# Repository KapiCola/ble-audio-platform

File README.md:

# BLE Audio Platform - Engineering Project

Custom hardware and firmware platform for prototyping and evaluating Bluetooth Low Energy Audio broadcast transmission.

This repository combines:
- custom PCB design created in KiCad
- firmware applications based on nRF Connect SDK and Zephyr RTOS
- component datasheets used during design and bring-up
- test logs and recorded audio collected during BLE Audio experiments

The platform is built around the BT40F SiP with the Nordic nRF5340 and was used to evaluate LE Audio broadcast transmission based on BIS streams.

## System Overview

Main hardware blocks:
- BT40F SiP with Nordic nRF5340
- Nordic nPM13xx PMIC (nPM1304 used in the assembled board as a practical substitute for nPM1300; the main functional difference is reduced battery-charging capability)
- CP2105 USB-UART bridge
- SGTL5000 external audio codec
- USB-C power and debug connectivity
- microphone, line output, and headphone audio connectors

## Repository Layout

```text
.
|-- Datasheets/   Component datasheets used during design and bring-up
|-- Firmware/     Zephyr/NCS applications, overlays, and helper modules
|-- Images/       Board photos, PCB renders, and architecture diagrams
|-- KiCad/        Schematic, PCB, project libraries, and Gerber outputs
`-- Tests_data/   Recorded audio samples and test logs
```

Important subdirectories:
- `Firmware/bap_broadcast_source/` BLE Audio broadcast source application
- `Firmware/bap_broadcast_sink/` BLE Audio broadcast sink application
- `Firmware/codec_test/` codec bring-up and audio-path verification
- `Firmware/test_i2c/` I2C and peripheral detection tests
- `Firmware/leds_test/` PMIC and LED bring-up
- `Firmware/beacon/` BLE beacon baseline application
- `Firmware/biblioteki/` shared helper modules such as `pmic` and `i2c_helpers`
- `KiCad/BT40F_audio_board_smaller/` main KiCad project
- `KiCad/Gerber/` exported manufacturing files
- `Tests_data/Test_Logs/` logs from lab and real-world experiments
- `Tests_data/Recorded_Audio/` captured audio files used during evaluation

Note: some directories inside `Firmware/` such as `build/`, `Build_V1/`, and `MyBoard/` are generated build outputs committed alongside the source tree. They are useful as build records, but they are not the primary source files to edit.

## Firmware Summary

The main project flow is built around two applications:
- `bap_broadcast_source` transmits BLE Audio broadcast streams
- `bap_broadcast_sink` receives BLE Audio broadcasts and contains project-specific modules for LC3 handling, USB, codec output, and stream reception

Additional applications are included for hardware validation and bring-up:
- `codec_test` initializes and probes the SGTL5000 path
- `test_i2c` verifies low-level I2C communication and peripheral presence
- `leds_test` validates PMIC-related control paths and LED behavior
- `beacon` provides a minimal BLE reference application

The per-application `README.rst` files under `Firmware/` are based on upstream Zephyr samples. For this repository, the project-specific behavior is defined mainly by the local `src/`, `boards/`, `*.overlay`, `prj.conf`, and `Kconfig*` files.

## Hardware Design

The hardware project contains:
- schematic and PCB layout files in `KiCad/BT40F_audio_board_smaller/`
- custom symbol and footprint libraries in `KiCad/BT40F_audio_board_smaller/Project libraries/`
- generated Gerbers in `KiCad/Gerber/BT40F_board_revA.zip`
- supporting visual assets in `Images/`

Some hardware files and library names still refer to `nPM1300`, while the assembled prototype used `nPM1304` because `nPM1300` was unavailable at the time. For this project, the devices are treated as near-equivalent except for the weaker charging capability of `nPM1304`.

## Building The Firmware

This repository does not include a full NCS workspace manifest, so builds are expected to run inside an existing nRF Connect SDK environment with `west` available.

Example commands reconstructed from the committed build artifacts:

```bash
west build --pristine --build-dir build/source-custom Firmware/bap_broadcast_source --board nrf5340_audio_dk/nrf5340/cpuapp -- -DEXTRA_CONF_FILE=boards/nrf5340_audio_dk_nrf5340_cpuapp.conf -DCONF_FILE=prj.conf -DEXTRA_DTC_OVERLAY_FILE=Custom_Board.overlay -DDTC_OVERLAY_FILE=app.overlay

west build --pristine --build-dir build/sink-custom Firmware/bap_broadcast_sink --board nrf5340_audio_dk/nrf5340/cpuapp -- -DEXTRA_CONF_FILE=boards/nrf5340_audio_dk_nrf5340_cpuapp.conf -DCONF_FILE=prj.conf -DEXTRA_DTC_OVERLAY_FILE=Custom_Board.overlay -DDTC_OVERLAY_FILE=app.overlay

west build --pristine --build-dir build/codec-test Firmware/codec_test --board nrf5340_audio_dk/nrf5340/cpuapp -- -DCONF_FILE=prj.conf -DDTC_OVERLAY_FILE=nrf5340_audio_dk_nrf5340_cpuapp.overlay
```

If you build one of the custom configurations, review the local overlays and board configuration files in the target application directory before flashing.

## Test Data

Test artifacts are grouped under `Tests_data/`:
- `Test_Logs/01_Lab_Tests/` source and sink logs captured in laboratory conditions
- `Test_Logs/02_Real_World_Tests/` logs collected in a more challenging radio environment
- `Test_Logs/03_Audio_Transmission_test/` dedicated source and sink logs for audio transmission checks
- `Recorded_Audio/` sample WAV captures

Due to memory constraints, logging on the Network Core was disabled. The provided logs come from the Application Core.

## Known Limitations

- The SGTL5000 codec could not be fully used in the final tests because the available MCU clocking was insufficient for the intended MCLK configuration
- Network Core logging was disabled because of memory constraints
- Final validation therefore focused on LC3 processing and BLE transmission rather than a fully closed audio path

## License

This project is licensed under the terms of the [LICENSE](LICENSE) file in this repository.

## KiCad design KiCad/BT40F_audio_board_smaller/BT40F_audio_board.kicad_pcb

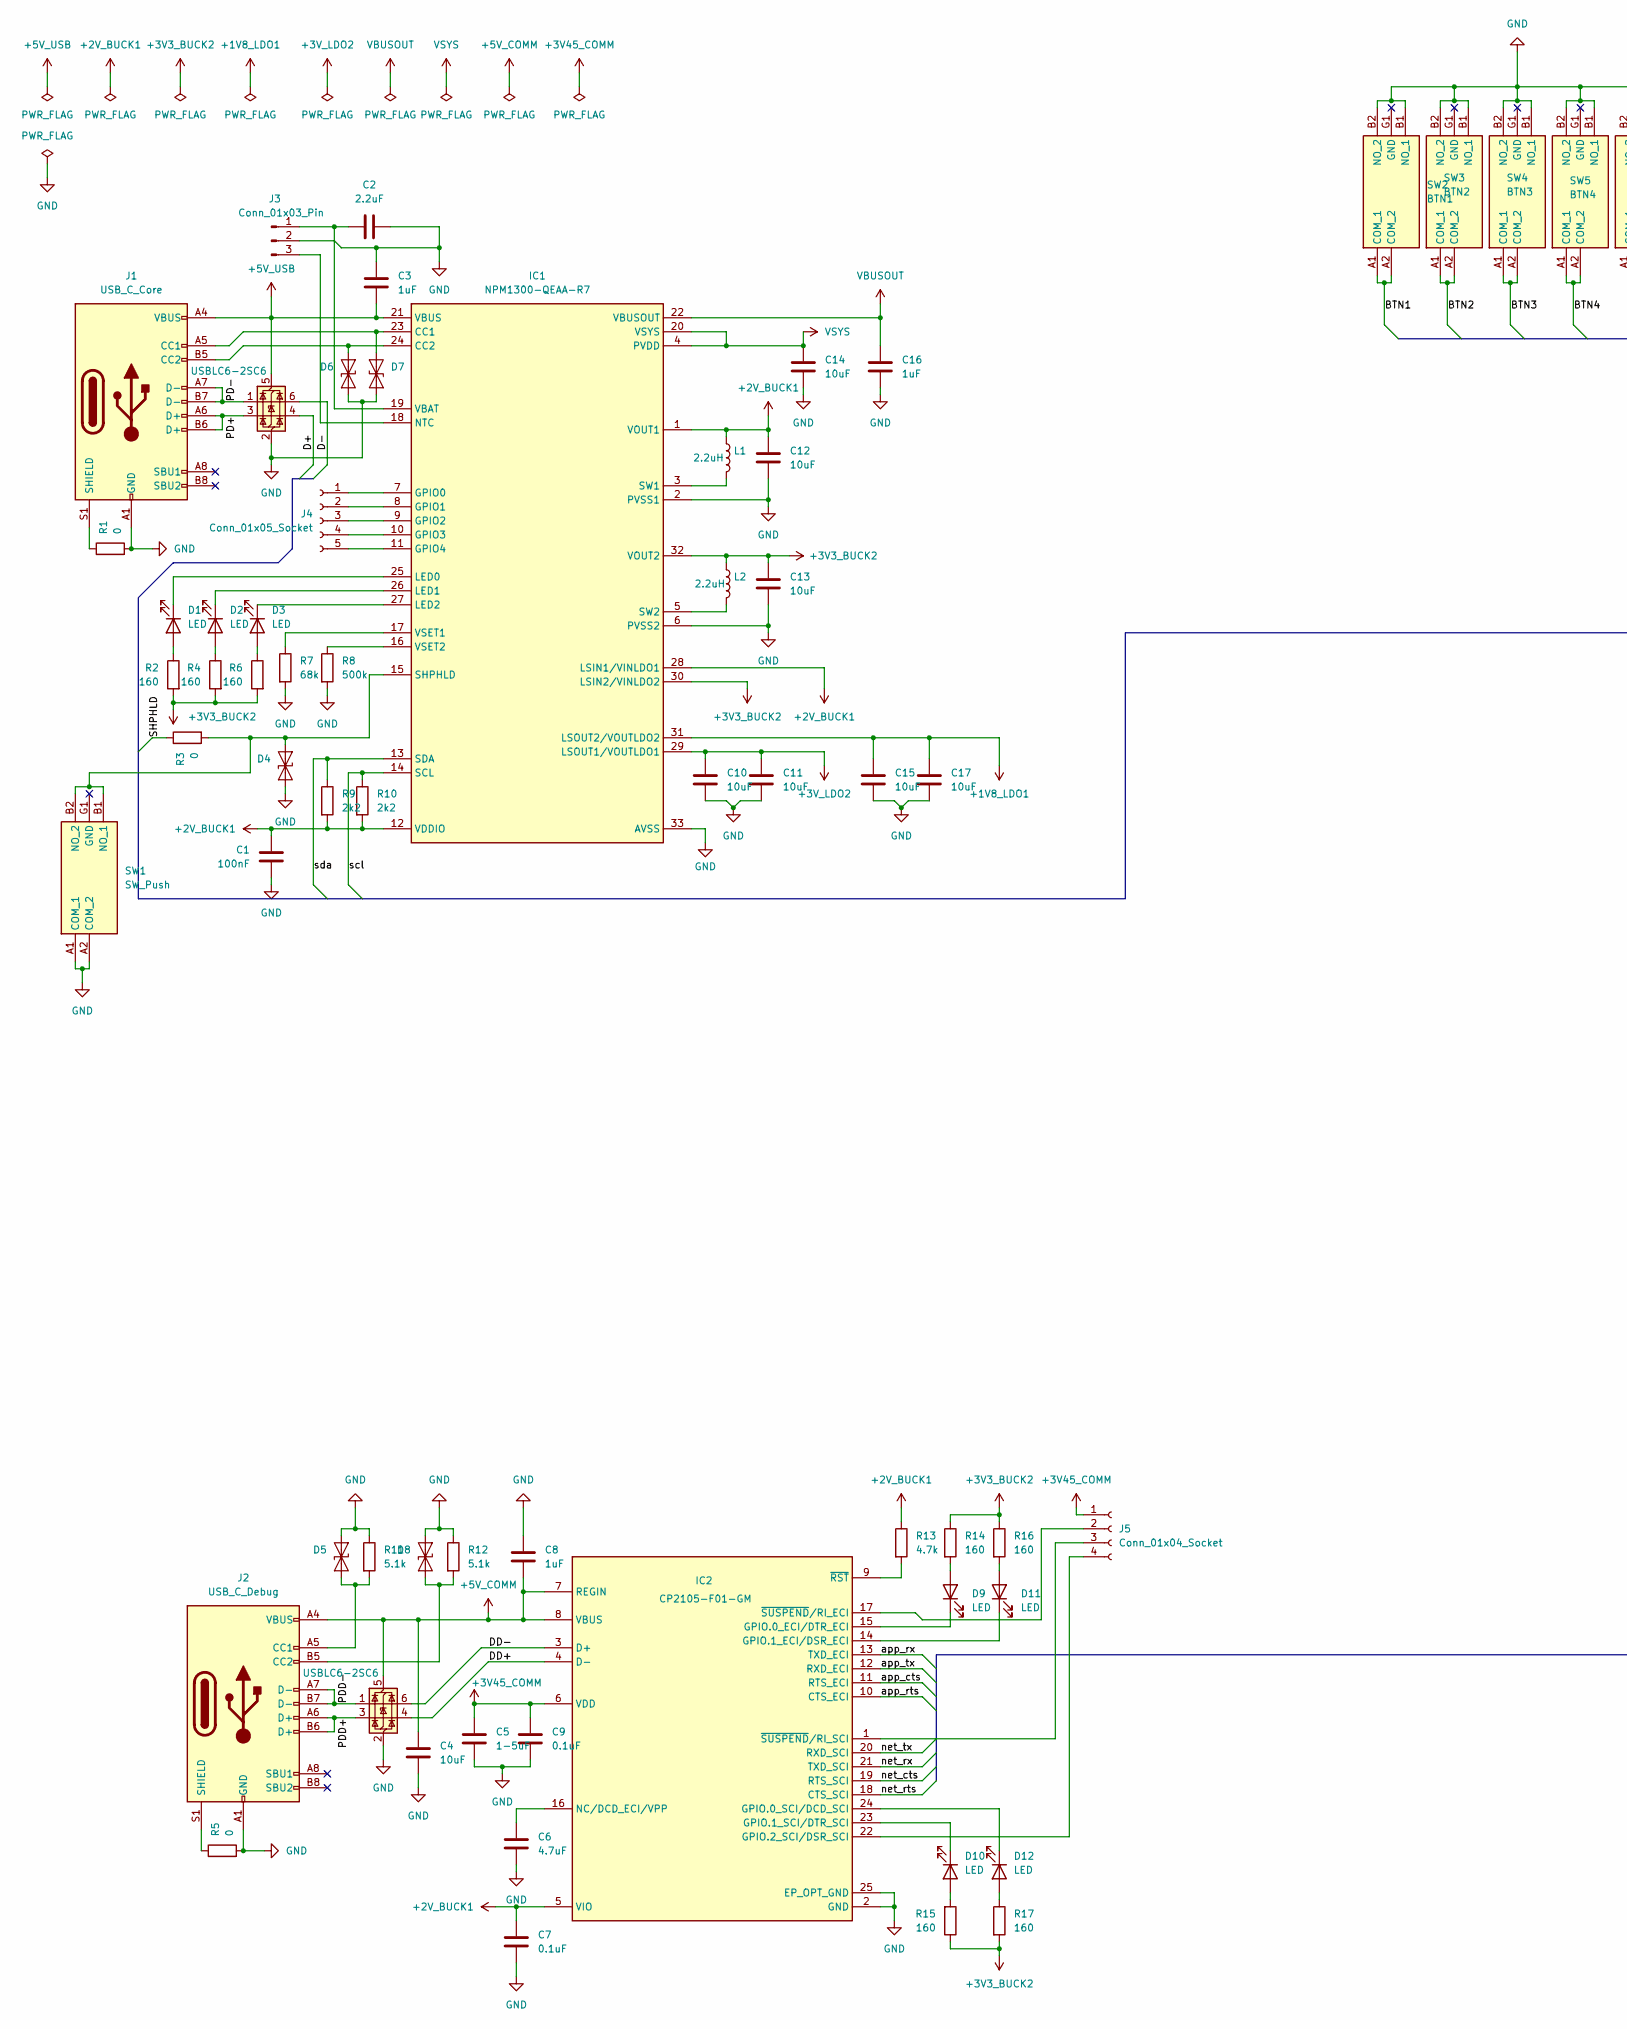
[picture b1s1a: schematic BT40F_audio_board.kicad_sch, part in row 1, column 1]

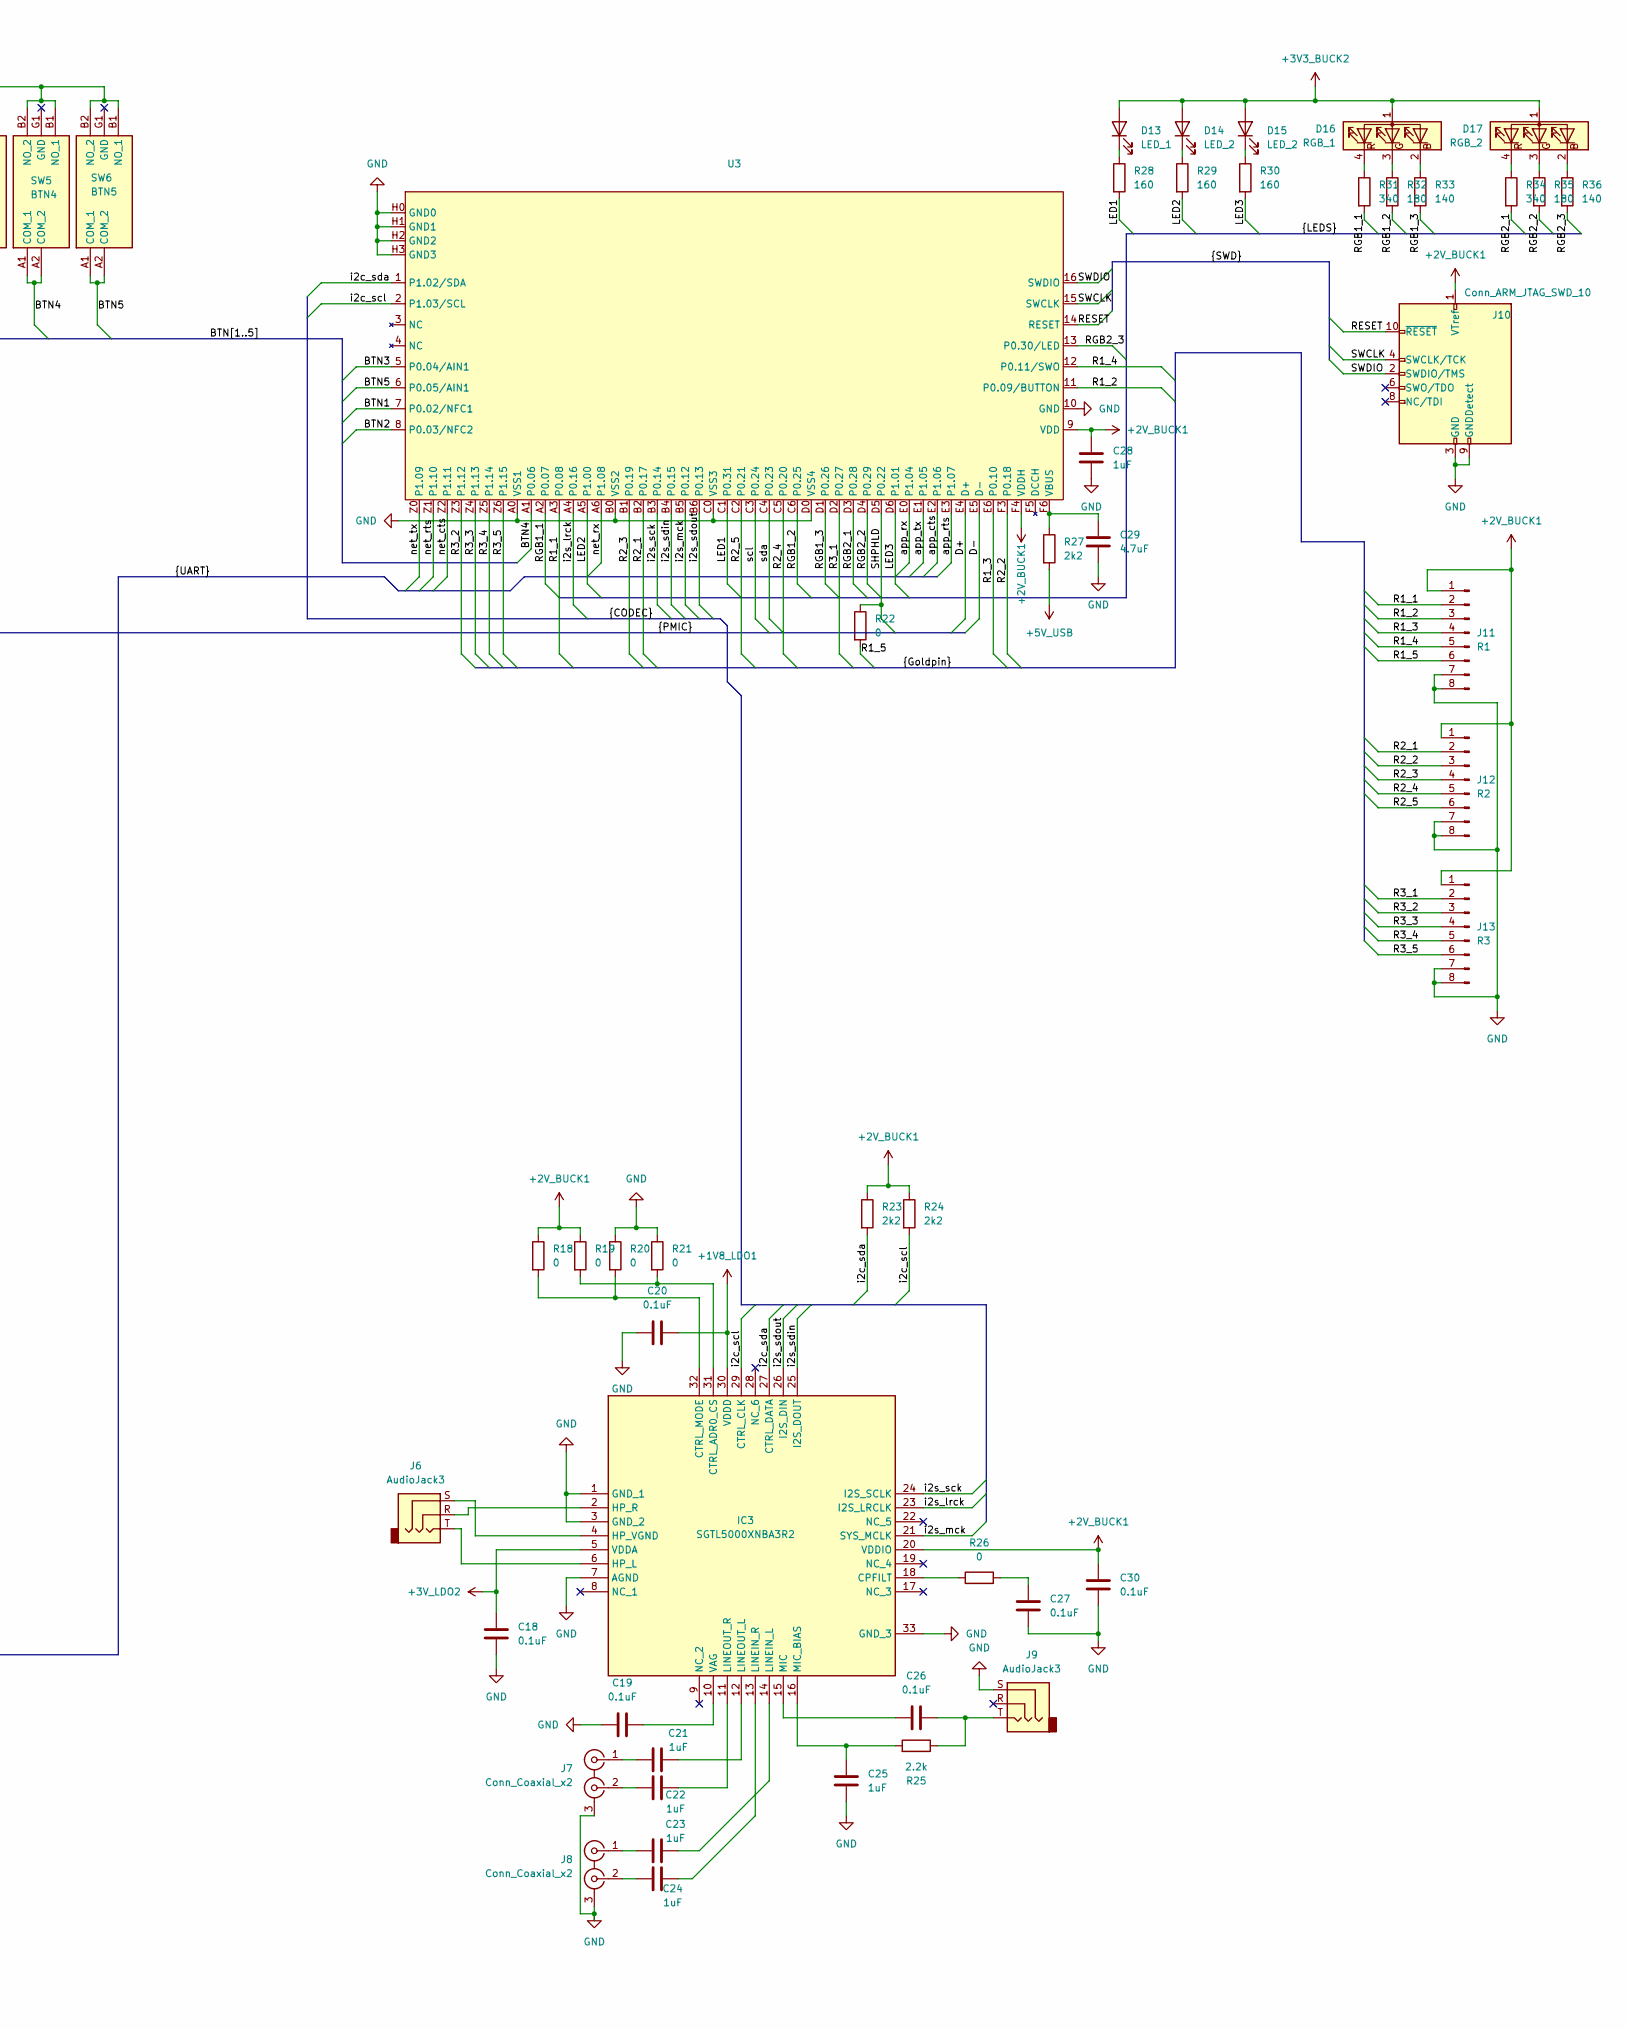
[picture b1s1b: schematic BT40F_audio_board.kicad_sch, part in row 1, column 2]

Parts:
C1: 100nF; C_0603_1608Metric_Pad1.08x0.95mm_HandSolder
C2: 2.2uF; C_0603_1608Metric_Pad1.08x0.95mm_HandSolder
C3, C8, C16, C25, C28: 1uF; C_0603_1608Metric_Pad1.08x0.95mm_HandSolder
C4, C10, C11, C12, C13, C14, C15, C17: 10uF; C_0603_1608Metric_Pad1.08x0.95mm_HandSolder
C5: 1-5uF; C_0603_1608Metric_Pad1.08x0.95mm_HandSolder
C6, C29: 4.7uF; C_0603_1608Metric_Pad1.08x0.95mm_HandSolder
C7, C9, C18, C20, C27, C30: 0.1uF; C_0603_1608Metric_Pad1.08x0.95mm_HandSolder
C19, C26: 0.1uF; Cap_foil_5mm
C21, C22, C23, C24: 1uF; R82_cap_raster_5mm
D1, D2, D3, D9, D10, D11, D12: LED; LED_0603_1608Metric_Pad1.05x0.95mm_HandSolder
D4, D5, D6, D7, D8: ESD; D_SOD-523
D13: LED_1; LED_0603_1608Metric_Pad1.05x0.95mm_HandSolder
D14, D15: LED_2; LED_0603_1608Metric_Pad1.05x0.95mm_HandSolder
D16: RGB_1; OSTB0603C1CA
D17: RGB_2; OSTB0603C1CA
IC1: NPM1300-QEAA-R7; Manufacturer_Part_Number NPM1300-QEAA-R7; Mouser Part Number 949-NPM1300-QEAA-R7
IC2: CP2105-F01-GM; Manufacturer_Part_Number CP2105-F01-GM; Mouser Part Number 634-CP2105-F01-GM
IC3: SGTL5000XNBA3R2; Manufacturer_Part_Number SGTL5000XNBA3R2; Mouser Part Number 771-SGTL5000XNBA3R2
J1: USB_C_Core; USB421603A
J2: USB_C_Debug; USB421603A
J3: Conn_01x03_Pin; PinHeader_1x03_P2.54mm_Horizontal
J4: Conn_01x05_Socket; PinHeader_1x05_P2.54mm_Vertical_SMD_Pin1Left
J5: Conn_01x04_Socket; PinHeader_1x04_P2.54mm_Vertical_SMD_Pin1Left
J6, J9: AudioJack3; 35RASMT2BHWNTRX
J7, J8: Conn_Coaxial_x2; FC68405
J10: Conn_ARM_JTAG_SWD_10; PinHeader_2x05_P1.27mm_Vertical_SMD
J11: R1; PinHeader_1x08_P2.54mm_Vertical_SMD_Pin1Left
J12: R2; PinHeader_1x08_P2.54mm_Vertical_SMD_Pin1Left
J13: R3; PinHeader_1x08_P2.54mm_Vertical_SMD_Pin1Left
L1, L2: 2.2uH; L_1008_2520Metric_Pad1.43x2.20mm_HandSolder
R1, R3, R5, R18, R19, R20, R21, R22, R26: 0; R_0603_1608Metric_Pad0.98x0.95mm_HandSolder
R2, R4, R6, R14, R15, R16, R17, R28, R29, R30: 160; R_0603_1608Metric_Pad0.98x0.95mm_HandSolder
R7: 68k; R_0603_1608Metric_Pad0.98x0.95mm_HandSolder
R8: 500k; R_0603_1608Metric_Pad0.98x0.95mm_HandSolder
R9, R10, R23, R24, R27: 2k2; R_0603_1608Metric_Pad0.98x0.95mm_HandSolder
R11, R12: 5.1k; R_0603_1608Metric_Pad0.98x0.95mm_HandSolder
R13: 4.7k; R_0603_1608Metric_Pad0.98x0.95mm_HandSolder
R25: 2.2k; R_0603_1608Metric_Pad0.98x0.95mm_HandSolder
R31, R34: 340; R_0603_1608Metric_Pad0.98x0.95mm_HandSolder
R32, R35: 180; R_0603_1608Metric_Pad0.98x0.95mm_HandSolder
R33, R36: 140; R_0603_1608Metric_Pad0.98x0.95mm_HandSolder
SW1: SW_Push; EVQQ2D02W; Manufacturer_Part_Number EVQQ2D02W
SW2: BTN1; EVQQ2D02W; Manufacturer_Part_Number EVQQ2D02W
SW3: BTN2; EVQQ2D02W; Manufacturer_Part_Number EVQQ2D02W
SW4: BTN3; EVQQ2D02W; Manufacturer_Part_Number EVQQ2D02W
SW5: BTN4; EVQQ2D02W; Manufacturer_Part_Number EVQQ2D02W
SW6: BTN5; EVQQ2D02W; Manufacturer_Part_Number EVQQ2D02W
U1, U2: USBLC6-2SC6; SOT-23-6
U3: XCVR_BT40F

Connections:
+1V8_LDO1: C15.1, C17.1, C20.2, IC1.31 (LSOUT2/VOUTLDO2), IC3.30 (VDDD)
+2V_BUCK1: C1.1, C7.1, C12.1, C28.1, C30.1, IC1.1 (VOUT1), IC1.12 (VDDIO), IC1.28 (LSIN1/VINLDO1), IC2.5 (VIO), IC3.20 (VDDIO), J10.1 (VTref), J11.1, J12.1, J13.1, L1.1, R9.2, R10.2, R13.1, R18.1, R19.1, R23.1, R24.1, U3.9 (VDD), U3.F4 (VDDH)
+3V3_BUCK2: C13.1, D13.2 (A), D14.2 (A), D15.2 (A), D16.1 (A), D17.1 (A), IC1.30 (LSIN2/VINLDO2), IC1.32 (VOUT2), L2.1, R2.2, R4.2, R6.2, R14.1, R15.1, R16.1, R17.2
+3V45_COMM: C5.1, C9.1, IC2.6 (VDD), J5.1
+3V_LDO2: C10.1, C11.1, C18.1, IC1.29 (LSOUT1/VOUTLDO1), IC3.5 (VDDA)
+5V_COMM: C4.1, C8.2, IC2.7 (REGIN), IC2.8 (VBUS), J2.A4 (VBUS), J2.A9 (VBUS), J2.B4 (VBUS), J2.B9 (VBUS), U2.5 (VBUS)
+5V_USB: C3.2, IC1.21 (VBUS), J1.A4 (VBUS), J1.A9 (VBUS), J1.B4 (VBUS), J1.B9 (VBUS), R27.2, U1.5 (VBUS)
/BTN1: SW2.A1 (COM_1), SW2.A2 (COM_2), U3.7 (P0.02/NFC1)
/BTN2: SW3.A1 (COM_1), SW3.A2 (COM_2), U3.8 (P0.03/NFC2)
/BTN3: SW4.A1 (COM_1), SW4.A2 (COM_2), U3.5 (P0.04/AIN1)
/BTN4: SW5.A1 (COM_1), SW5.A2 (COM_2), U3.A1 (P0.06)
/BTN5: SW6.A1 (COM_1), SW6.A2 (COM_2), U3.6 (P0.05/AIN1)
/D+: U1.4 (I/O2), U3.E4 (D+)
/D-: U1.6 (I/O1), U3.E5 (D-)
/DD+: IC2.4 (D-), U2.4 (I/O2)
/DD-: IC2.3 (D+), U2.6 (I/O1)
/LED1: R28.2, U3.C1 (P0.31)
/LED2: R29.2, U3.A5 (P1.00)
/LED3: R30.2, U3.D6 (P1.01)
/PD+: J1.A6 (D+), J1.B6 (D+), U1.3 (I/O2)
/PD-: J1.A7 (D-), J1.B7 (D-), U1.1 (I/O1)
/PDD+: J2.A6 (D+), J2.B6 (D+), U2.3 (I/O2)
/PDD-: J2.A7 (D-), J2.B7 (D-), U2.1 (I/O1)
/R1_1: J11.2, U3.A3 (P0.08)
/R1_2: J11.3, U3.11 (P0.09/BUTTON)
/R1_3: J11.4, U3.E6 (P0.10)
/R1_4: J11.5, U3.12 (P0.11/SWO)
/R1_5: J11.6, R22.2
/R2_1: J12.2, U3.B2 (P0.17)
/R2_2: J12.3, U3.F3 (P0.18)
/R2_3: J12.4, U3.B1 (P0.19)
/R2_4: J12.5, U3.C5 (P0.20)
/R2_5: J12.6, U3.C2 (P0.21)
/R3_1: J13.2, U3.D2 (P0.27)
/R3_2: J13.3, U3.Z3 (P1.12)
/R3_3: J13.4, U3.Z4 (P1.13)
/R3_4: J13.5, U3.Z5 (P1.14)
/R3_5: J13.6, U3.Z6 (P1.15)
/RESET: J10.10 (~RESET), U3.14 (RESET)
/RGB1_1: R31.2, U3.A2 (P0.07)
/RGB1_2: R32.2, U3.C6 (P0.25)
/RGB1_3: R33.2, U3.D1 (P0.26)
/RGB2_1: R34.2, U3.D3 (P0.28)
/RGB2_2: R35.2, U3.D4 (P0.29)
/RGB2_3: R36.2, U3.13 (P0.30/LED)
/SHPHLD: R3.1, R22.1, U3.D5 (P0.22)
/SWCLK: J10.4 (SWCLK/TCK), U3.15 (SWCLK)
/SWDIO: J10.2 (SWDIO/TMS), U3.16 (SWDIO)
/app_cts: IC2.11 (RTS_ECI), U3.E2 (P1.06)
/app_rts: IC2.10 (CTS_ECI), U3.E3 (P1.07)
/app_rx: IC2.13 (TXD_ECI), U3.E0 (P1.04)
/app_tx: IC2.12 (RXD_ECI), U3.E1 (P1.05)
/i2c_scl: IC3.29 (CTRL_CLK), R24.2, U3.2 (P1.03/SCL)
/i2c_sda: IC3.27 (CTRL_DATA), R23.2, U3.1 (P1.02/SDA)
/i2s_lrck: IC3.23 (I2S_LRCLK), U3.A4 (P0.16)
/i2s_mck: IC3.21 (SYS_MCLK), U3.B5 (P0.12)
/i2s_sck: IC3.24 (I2S_SCLK), U3.B3 (P0.14)
/i2s_sdin: IC3.25 (I2S_DOUT), U3.B4 (P0.15)
/i2s_sdout: IC3.26 (I2S_DIN), U3.B6 (P0.13)
/net_cts: IC2.19 (RTS_SCI), U3.Z2 (P1.11)
/net_rts: IC2.18 (CTS_SCI), U3.Z1 (P1.10)
/net_rx: IC2.21 (TXD_SCI), U3.A6 (P1.08)
/net_tx: IC2.20 (RXD_SCI), U3.Z0 (P1.09)
/scl: IC1.14 (SCL), R10.1, U3.C3 (P0.24)
/sda: IC1.13 (SDA), R9.1, U3.C4 (P0.23)
GND: C1.2, C2.2, C3.1, C4.2, C5.2, C6.2, C7.2, C8.1, C9.2, C10.2, C11.2, C12.2, C13.2, C14.2, C15.2, C16.2, C17.2, C18.2, C19.1, C20.1, C25.2, C27.2, C28.2, C29.2, C30.2, D4.1 (A1), D5.2 (A2), D6.1 (A1), D7.1 (A1), D8.2 (A2), IC1.2 (PVSS1), IC1.6 (PVSS2), IC1.33 (AVSS), IC2.2 (GND), IC2.25 (EP_OPT_GND), IC3.1 (GND_1), IC3.3 (GND_2), IC3.7 (AGND), IC3.33 (GND_3), J1.A1 (GND), J1.A12 (GND), J1.B1 (GND), J1.B12 (GND), J2.A1 (GND), J2.A12 (GND), J2.B1 (GND), J2.B12 (GND), J3.2, J7.3 (EXT), J8.3 (EXT), J9.S, J10.3 (GND), J10.5 (GND), J10.9 (GNDDetect), J11.7, J11.8, J12.7, J12.8, J13.7, J13.8, R1.2, R5.2, R7.2, R8.2, R11.1, R12.1, R20.1, R21.1, SW1.A1 (COM_1), SW1.A2 (COM_2), SW2.B1 (NO_1), SW2.B2 (NO_2), SW3.B1 (NO_1), SW3.B2 (NO_2), SW4.B1 (NO_1), SW4.B2 (NO_2), SW5.B1 (NO_1), SW5.B2 (NO_2), SW6.B1 (NO_1), SW6.B2 (NO_2), U1.2 (GND), U2.2 (GND), U3.10 (GND), U3.A0 (VSS1), U3.B0 (VSS2), U3.C0 (VSS3), U3.D0 (VSS4), U3.H0 (GND0), U3.H1 (GND1), U3.H2 (GND2), U3.H3 (GND3)
unnamed: C26.2, J9.T, R25.1
unnamed: C27.1, R26.2
unnamed: D1.2 (A), R2.1
unnamed: D1.1 (K), IC1.25 (LED0)
unnamed: D2.2 (A), R4.1
unnamed: D2.1 (K), IC1.26 (LED1)
unnamed: D3.2 (A), R6.1
unnamed: D3.1 (K), IC1.27 (LED2)
unnamed: D4.2 (A2), IC1.15 (SHPHLD), R3.2, SW1.B1 (NO_1), SW1.B2 (NO_2)
unnamed: D5.1 (A1), J2.A5 (CC1), R11.2
unnamed: D6.2 (A2), IC1.24 (CC2), J1.B5 (CC2)
unnamed: D7.2 (A2), IC1.23 (CC1), J1.A5 (CC1)
unnamed: D8.1 (A1), J2.B5 (CC2), R12.2
unnamed: D9.2 (A), R14.2
unnamed: D9.1 (K), IC2.15 (GPIO.0_ECI/DTR_ECI)
unnamed: D10.2 (A), R15.2
unnamed: D10.1 (K), IC2.23 (GPIO.1_SCI/DTR_SCI)
unnamed: D11.2 (A), R16.2
unnamed: D11.1 (K), IC2.14 (GPIO.1_ECI/DSR_ECI)
unnamed: D12.2 (A), R17.1
unnamed: D12.1 (K), IC2.24 (GPIO.0_SCI/DCD_SCI)
unnamed: D13.1 (K), R28.1
unnamed: D14.1 (K), R29.1
unnamed: D15.1 (K), R30.1
unnamed: D16.2 (BK), R33.1
unnamed: D16.3 (GK), R32.1
unnamed: D16.4 (RK), R31.1
unnamed: D17.2 (BK), R36.1
unnamed: D17.3 (GK), R35.1
unnamed: D17.4 (RK), R34.1
unnamed: IC1.7 (GPIO0), J4.1
unnamed: IC1.8 (GPIO1), J4.2
unnamed: IC1.9 (GPIO2), J4.3
unnamed: IC1.10 (GPIO3), J4.4
unnamed: IC1.11 (GPIO4), J4.5
unnamed: IC1.18 (NTC), J3.3
unnamed: IC1.3 (SW1), L1.2
unnamed: IC1.5 (SW2), L2.2
unnamed: C2.1, IC1.19 (VBAT), J3.1
unnamed: IC1.17 (VSET1), R7.1
unnamed: IC1.16 (VSET2), R8.1
unnamed: IC2.22 (GPIO.2_SCI/DSR_SCI), J5.4
unnamed: C6.1, IC2.16 (NC/DCD_ECI/VPP)
unnamed: IC2.9 (~RST), R13.2
unnamed: IC2.17 (~SUSPEND/RI_ECI), J5.2
unnamed: IC2.1 (~SUSPEND/RI_SCI), J5.3
unnamed: IC3.18 (CPFILT), R26.1
unnamed: IC3.31 (CTRL_ADR0_CS), R19.2, R21.2
unnamed: IC3.32 (CTRL_MODE), R18.2, R20.2
unnamed: IC3.6 (HP_L), J6.T
unnamed: IC3.2 (HP_R), J6.R
unnamed: IC3.4 (HP_VGND), J6.S
unnamed: C23.1, IC3.14 (LINEIN_L)
unnamed: C24.1, IC3.13 (LINEIN_R)
unnamed: C21.1, IC3.12 (LINEOUT_L)
unnamed: C22.1, IC3.11 (LINEOUT_R)
unnamed: C26.1, IC3.15 (MIC)
unnamed: C25.1, IC3.16 (MIC_BIAS), R25.2
unnamed: C19.2, IC3.10 (VAG)
unnamed: J1.S1 (SHIELD), R1.1
unnamed: J2.S1 (SHIELD), R5.1
unnamed: C21.2, J7.1 (IN1)
unnamed: C22.2, J7.2 (IN2)
unnamed: C23.2, J8.1 (IN1)
unnamed: C24.2, J8.2 (IN2)
unnamed: C29.1, R27.1, U3.F6 (VBUS)
VBUSOUT: C16.1, IC1.22 (VBUSOUT)
VSYS: C14.1, IC1.4 (PVDD), IC1.20 (VSYS)

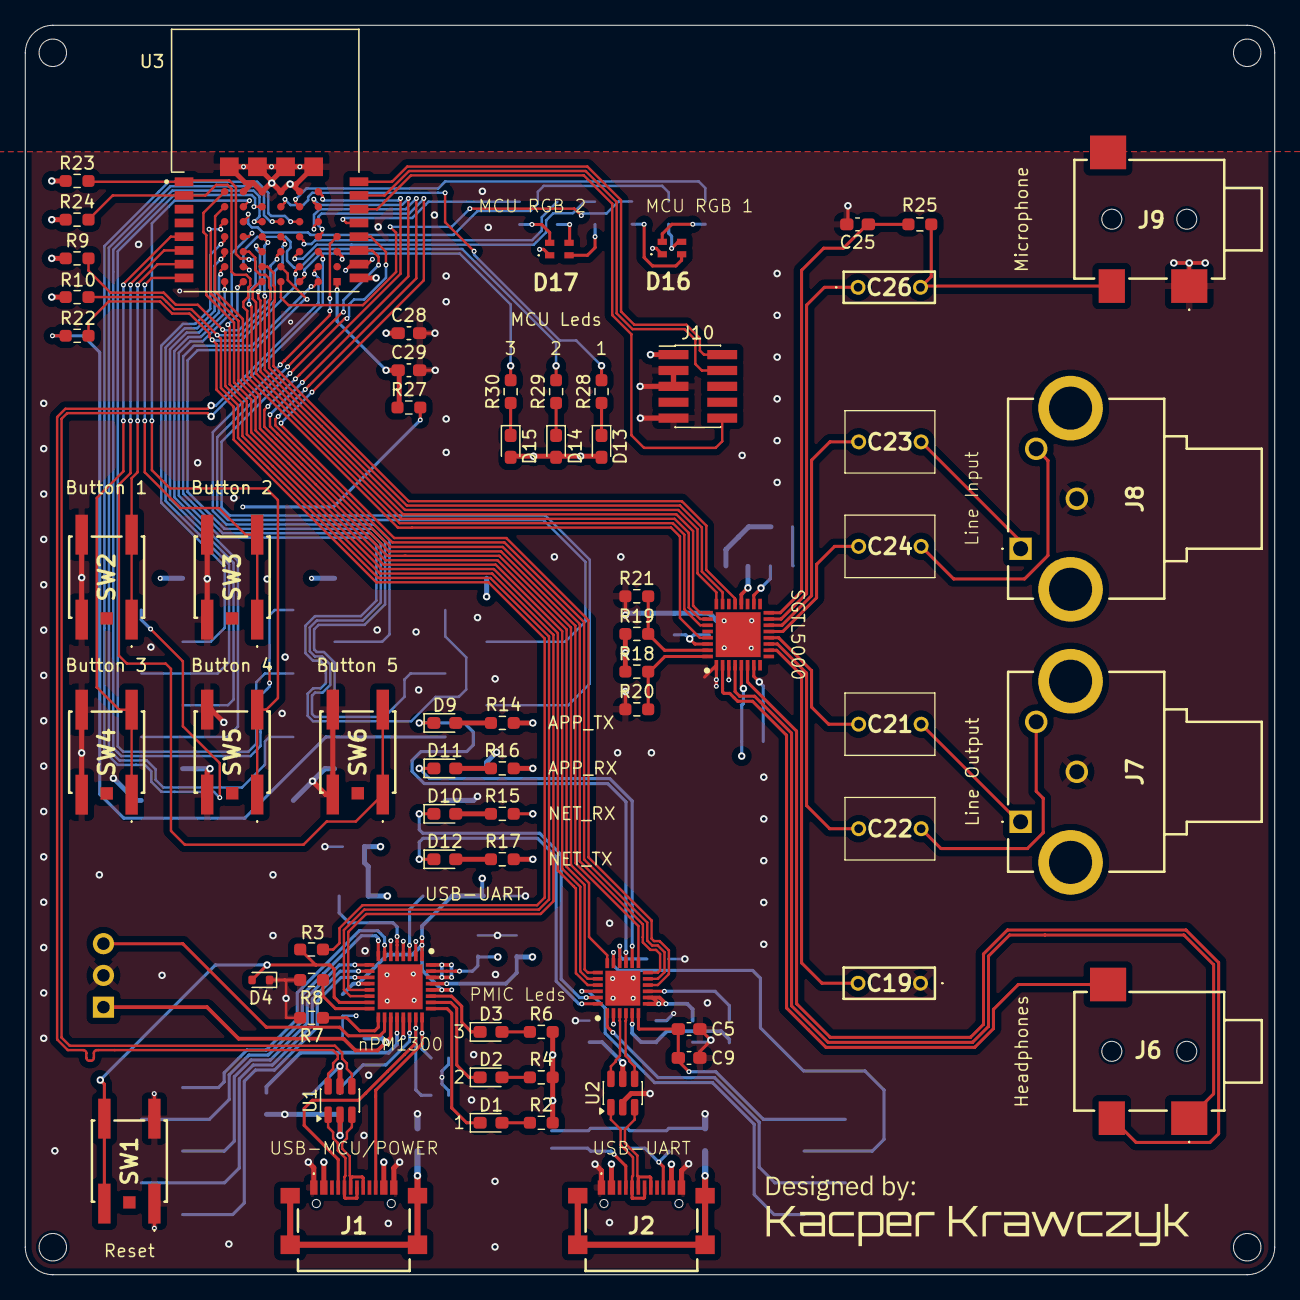
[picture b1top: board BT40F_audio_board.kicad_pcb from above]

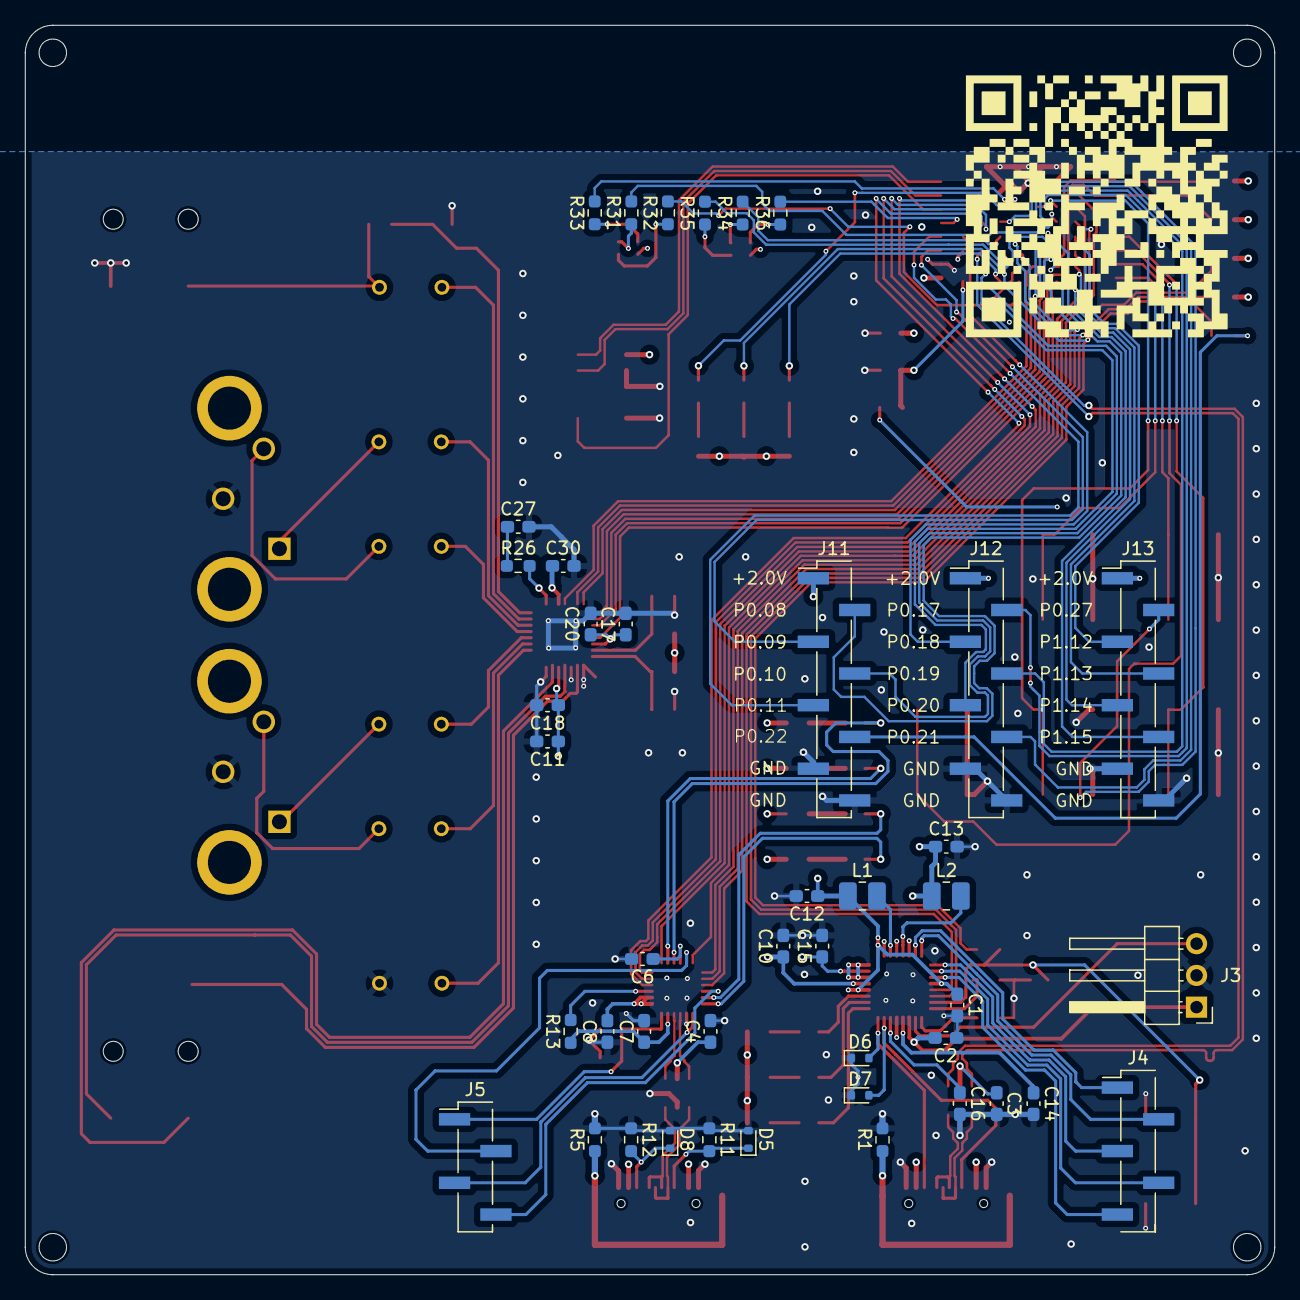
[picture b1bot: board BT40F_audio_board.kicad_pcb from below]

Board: 4 copper layers, 100.0 x 100.0 mm, 110 parts (43 on the bottom side), 134 nets.

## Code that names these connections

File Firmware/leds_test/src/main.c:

#include <zephyr/kernel.h>
#include <zephyr/device.h>
#include <zephyr/devicetree.h>
#include <zephyr/drivers/gpio.h>
#include "pmic.h"

#define SLEEP_TIME_MS (1000)

#define NUM_BUTTONS 5
#define NUM_LEDS    9

static int64_t last_press[NUM_BUTTONS];

static const struct gpio_dt_spec buttons[NUM_BUTTONS] = {
    GPIO_DT_SPEC_GET(DT_ALIAS(sw0), gpios),
    GPIO_DT_SPEC_GET(DT_ALIAS(sw1), gpios),
    GPIO_DT_SPEC_GET(DT_ALIAS(sw2), gpios),
    GPIO_DT_SPEC_GET(DT_ALIAS(sw3), gpios),
    GPIO_DT_SPEC_GET(DT_ALIAS(sw4), gpios),
};

static const struct gpio_dt_spec leds[NUM_LEDS] = {
    GPIO_DT_SPEC_GET(DT_ALIAS(led0), gpios),
    GPIO_DT_SPEC_GET(DT_ALIAS(led1), gpios),
    GPIO_DT_SPEC_GET(DT_ALIAS(led2), gpios),
    GPIO_DT_SPEC_GET(DT_ALIAS(led3), gpios),
    GPIO_DT_SPEC_GET(DT_ALIAS(led4), gpios),
    GPIO_DT_SPEC_GET(DT_ALIAS(led5), gpios),
    GPIO_DT_SPEC_GET(DT_ALIAS(led6), gpios),
    GPIO_DT_SPEC_GET(DT_ALIAS(led7), gpios),
    GPIO_DT_SPEC_GET(DT_ALIAS(led8), gpios),
};

static struct gpio_callback button_cbs[NUM_BUTTONS];

void button_pressed(const struct device *dev,
                    struct gpio_callback *cb,
                    uint32_t pins)
{
        int64_t now = k_uptime_get();
          
        for (int i = 0; i < NUM_BUTTONS; i++) {
                if ((cb == &button_cbs[i]) &&(pins & BIT(buttons[i].pin))) {

                        if (now - last_press[i] > 200) {
                                gpio_pin_toggle_dt(&leds[i+4]);
                                last_press[i] = now;
                        }

                break;
                }
        }
}

int main(void)
{
        int ret;
        //Inicjalizacja przetwornicy
        if (pmic_init() != 0) {
                return -1;
        }

        for (int i = 0; i < NUM_LEDS; i++) {
                if (!device_is_ready(leds[i].port)) return -1;
                gpio_pin_configure_dt(&leds[i], GPIO_OUTPUT_INACTIVE);
        }

	for (int i = 0; i < NUM_BUTTONS; i++) {
        if (!device_is_ready(buttons[i].port)) return -1;

                gpio_pin_configure_dt(&buttons[i], GPIO_INPUT | GPIO_PULL_UP);

                gpio_pin_interrupt_configure_dt(&buttons[i], GPIO_INT_EDGE_TO_ACTIVE);

                gpio_init_callback(&button_cbs[i],
                                button_pressed,
                                BIT(buttons[i].pin));

                gpio_add_callback(buttons[i].port, &button_cbs[i]);
        }

        pmic_led_off(0);
        pmic_led_off(1);
        pmic_led_off(2);

        while (1) {
		k_msleep(SLEEP_TIME_MS);
	}
}

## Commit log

2026-04-13 Add firmware sources and fix nested repositories
2026-04-18 Added codec initialization and simple passthrough
2026-04-18 Codec test with initialization
2026-04-20 Updated firmware to test audio and test results
2026-04-20 Modified README.md
2026-04-20 README.md for test modified
